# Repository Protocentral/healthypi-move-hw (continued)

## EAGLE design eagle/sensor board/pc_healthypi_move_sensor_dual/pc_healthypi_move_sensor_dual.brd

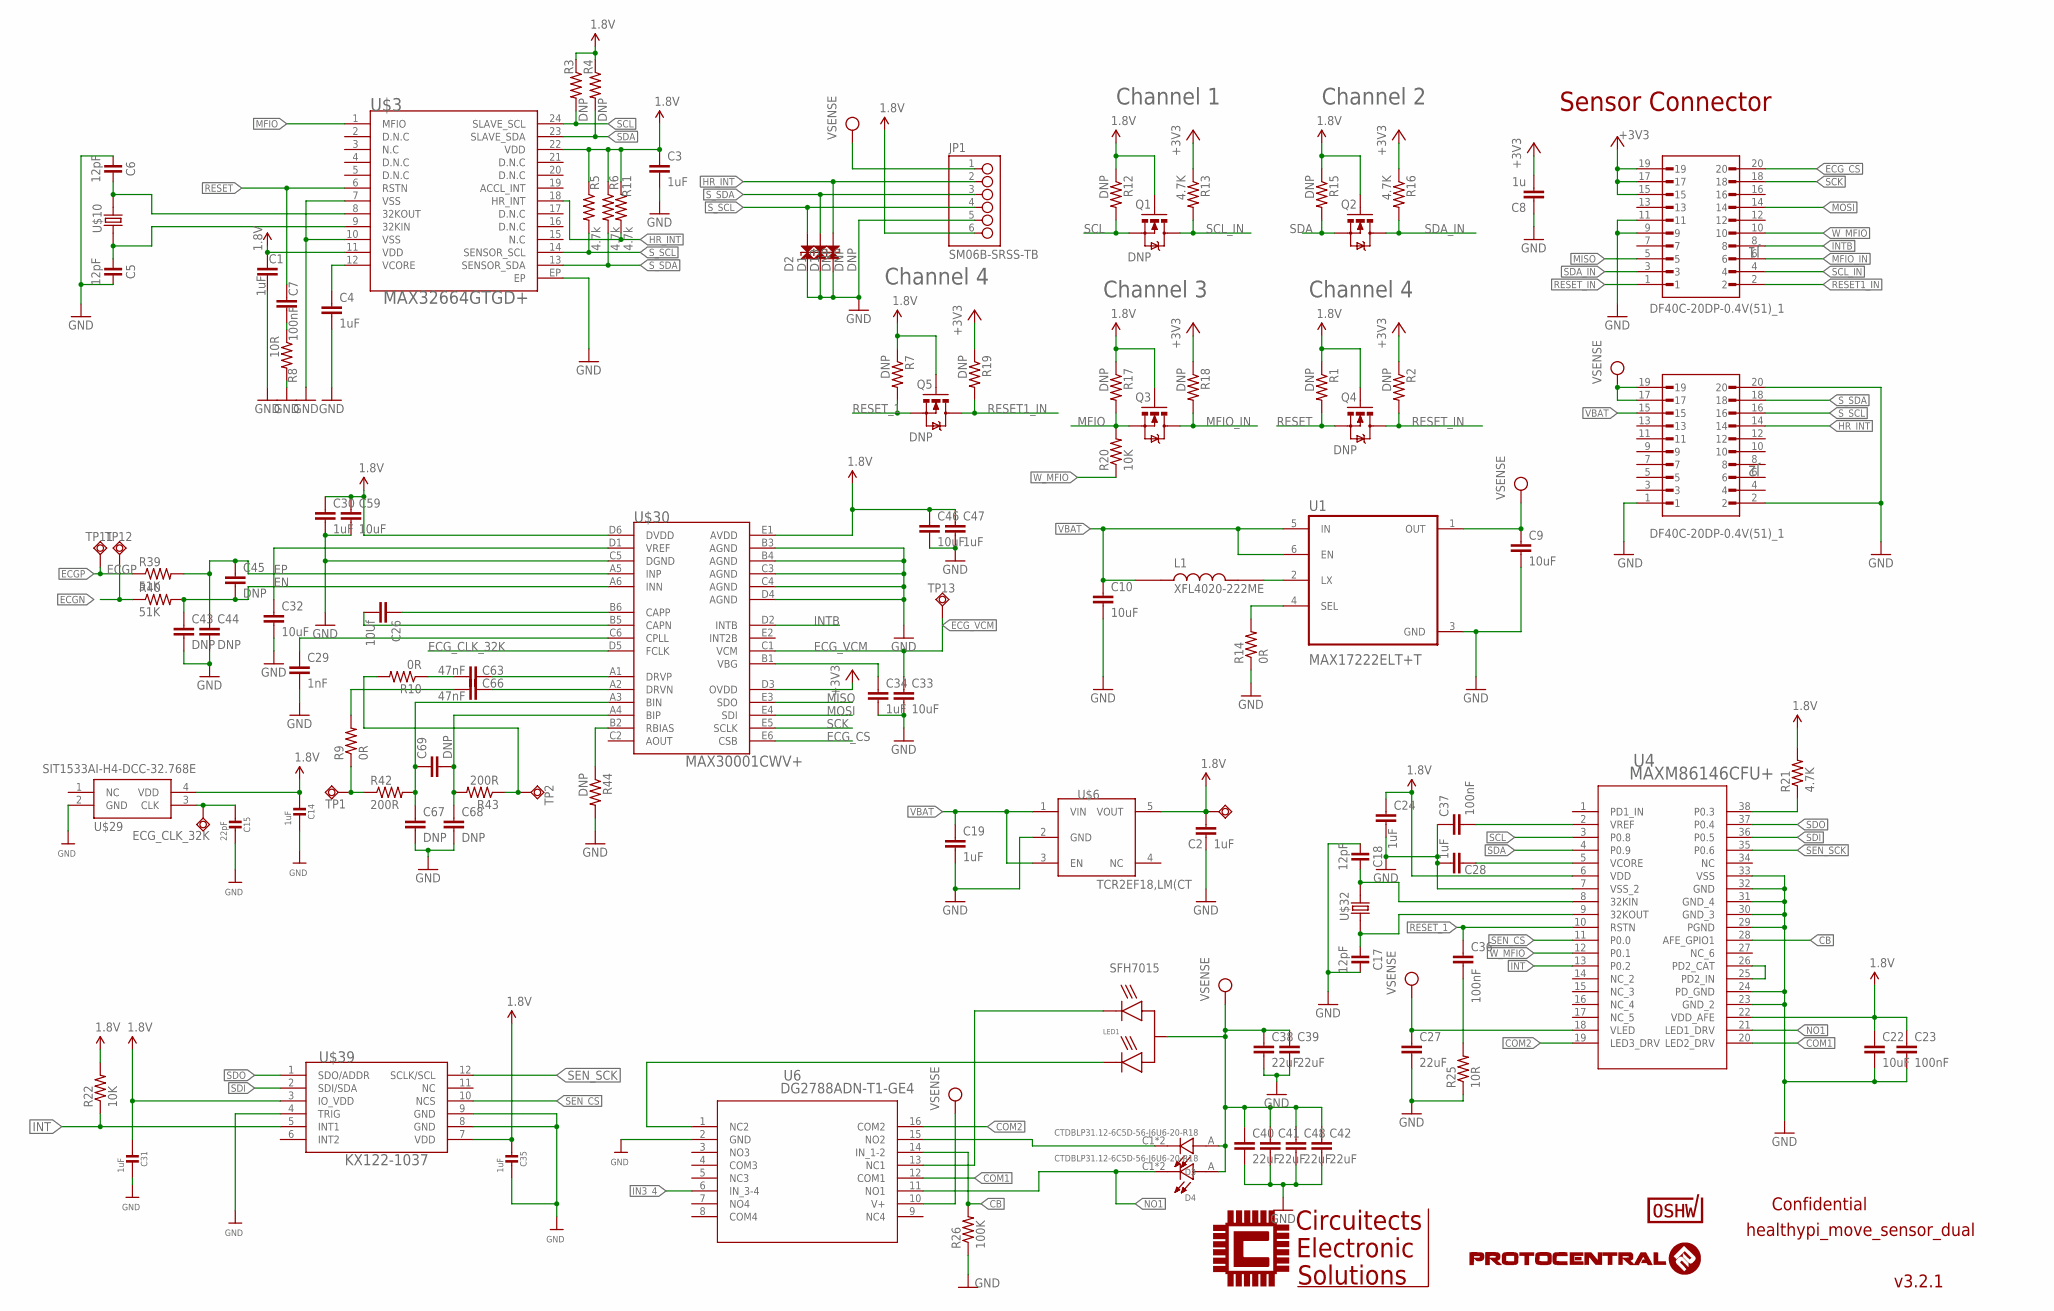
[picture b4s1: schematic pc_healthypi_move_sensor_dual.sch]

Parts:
C1, C2, C3, C4, C19, C24, C28, C30, C34, C47: 1uF; C0402
C5, C6, C17, C18: 12pF; C0402
C7, C23, C36, C37: 100nF; C0402
C8: 1u; C0402
C9, C10, C22, C32, C33, C46, C59: 10uF; C0402
C14, C31, C35: 1uF; 0402
C15: 22pF; 0402
C26: 10Uf; C0402
C27, C38, C39, C40, C41, C42, C48: 22uF; C0805
C29: 1nF; C0402
C43, C44, C45, C67, C68, C69: DNP; C0402
C63, C66: 47nF; C0402
D1, D2, D13: DNP; 0402
D3, D4: CTDBLP31.12-6C5D-56-J6U6-20-R18; LED_CTDBLP31.12-6C5D-56-J6U6-20-R18
J1, J2: DF40C-20DP-0.4V(51)_1; HRS_DF40C-20DP-0.4V(51)
JP1: SM06B-SRSS-TB
L1: XFL4020-222ME; IND_XFL4020-222ME
LED1: SFH7015
Q1, Q2, Q3, Q4, Q5: DNP; SOT23-3
R1, R2, R3, R4, R7, R12, R15, R17, R18, R19, R44: DNP; 0402-RES
R5, R6, R11: 4.7k; 0402-RES
R8: 10R; 0402-RES
R9, R10: 0R; 0402-RES
R13, R16: 4.7K; 0402-RES
R14: 0R; R0402
R20, R22: 10K; 0402-RES
R21: 4.7K; R0402
R25: 10R; R0402
R26: 100K; R0402
R39, R40: 51K; 0402-RES
R42, R43: 200R; 0402-RES
SWIO1, SWIO5: TPSQTP11R; TP11R
TP1, TP2, TP11, TP12, TP13: TPSQTP20SQ; TP20SQ
U1: MAX17222ELT+T; SON65P200X200X80-6N
U4: MAXM86146CFU+; 21-100323A_90-100112A_MXM
U6: DG2788ADN-T1-GE4; MINIQFN-16_VIS
U$3: MAX32664GTGD+; TQFN-24L
U$6: TCR2EF18,LM(CT; SOT95P285X140-5N
U$10, U$32: 520-327-12.5-34B(32.768KHZ); ECX-31B
U$29: SIT1533AI-H4-DCC-32.768E; SIT1533
U$30: MAX30001CWV+; 30WLP
U$39: KX122-1037; KIONIX_KXTJ3-1057
U$48: CERT-SMALL; CERT-SMALL-SILK

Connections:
1.8V: C1.1, C2.1, C3.1, C14.1, C22.1, C23.1, C24.1, C30.1, C31.1, C35.1, C46.1, C47.1, C59.1, JP1.6, Q1.1 (G), Q2.1 (G), Q3.1 (G), Q4.1 (G), Q5.1 (G), R1.1, R3.1, R4.1, R5.1, R6.1, R7.1, R11.1, R12.1, R15.1, R17.1, R21.2, R22.2, SWIO5.TP, U4.6 (VDD), U4.22 (VDD_AFE), U$3.11 (VDD), U$3.22 (VDD), U$6.5 (VOUT), U$29.4 (VDD), U$30.D6 (DVDD), U$30.E1 (AVDD), U$39.3 (IO_VDD), U$39.7 (VDD)
+3V3: C8.2, J1.15, J1.17, J1.19, R2.1, R13.1, R16.1, R18.1, R19.1, U$30.D3 (OVDD)
BIAZP: R10.2, R43.1, TP2.TP
BIOZN: R9.1, R42.1, TP1.TP
CB: R26.2, U4.28 (AFE_GPIO1), U6.14 (IN_1-2)
CLK_32K: C5.1, U$3.9 (32KIN), U$10.P$1 (1)
CLK_32K1: C17.1, U4.9 (32KOUT), U$32.P$1 (1)
COM1: U4.20 (LED2_DRV), U6.12 (COM1)
COM2: U4.19 (LED3_DRV), U6.16 (COM2)
ECGN: R40.1, TP12.TP
ECGP: R39.1, TP11.TP
ECG_CLK_32K: C15.1, SWIO1.TP, U$29.3 (CLK), U$30.D5 (FCLK)
ECG_CS: J1.20, U$30.E6 (CSB)
ECG_VCM: C33.1, TP13.TP, U$30.C1 (VCM)
EN: C43.1, C45.2, R40.2, U$30.A6 (INN)
EP: C44.1, C45.1, R39.2, U$30.A5 (INP)
GND: C1.2, C2.2, C3.2, C4.2, C5.2, C6.1, C8.1, C9.2, C10.2, C14.2, C15.2, C17.2, C18.1, C19.2, C22.2, C23.2, C24.2, C27.2, C28.2, C29.2, C30.2, C31.2, C32.2, C33.2, C34.2, C35.2, C37.1, C38.2, C39.2, C40.2, C41.2, C42.2, C43.2, C44.2, C46.2, C47.2, C48.2, C59.2, C67.2, C68.2, D1.1, D2.1, D13.1, J1.9, J1.11, J2.1, J2.2, J2.20, JP1.5, R8.2, R14.1, R25.1, R26.1, R44.2, U1.3 (GND), U4.7 (VSS_2), U4.23 (GND_2), U4.24 (PD_GND), U4.29 (PGND), U4.30 (GND_3), U4.31 (GND_4), U4.32 (GND), U4.33 (VSS), U6.2 (GND), U$3.7 (VSS), U$3.10 (VSS), U$3.EP, U$6.2 (GND), U$29.2 (GND), U$30.B3 (AGND), U$30.B4 (AGND), U$30.C3 (AGND), U$30.C4 (AGND), U$30.C5 (DGND), U$30.D4 (AGND), U$39.4 (TRIG), U$39.8 (GND), U$39.9 (GND)
HR_INT: D13.2, J2.14, JP1.2, R11.2, U$3.18 (HR_INT)
IN3_4: U6.6 (IN_3-4)
INT: R22.1, U4.13 (P0.2), U$39.5 (INT1)
INTB: J1.8, U$30.D2 (INTB)
MFIO: Q3.2 (S), R17.2, R20.2, U$3.1 (MFIO)
MFIO_IN: J1.6, Q3.3 (D), R18.2
MISO: J1.5, U$30.E3 (SDO)
MOSI: J1.14, U$30.E4 (SDI)
unnamed: C4.1, U$3.12 (VCORE)
unnamed: C7.2, R8.1
unnamed: R14.2, U1.4 (SEL)
unnamed: L1.2, U1.2 (LX)
unnamed: C18.2, U4.8 (32KIN), U$32.P$2 (2)
unnamed: U4.25 (PD2_IN), U4.26 (PD2_CAT)
unnamed: C28.1, U4.5 (VCORE)
unnamed: R21.1, U4.38 (P0.3)
unnamed: C37.2, U4.2 (VREF)
unnamed: C36.2, R25.2
unnamed: C66.1, R9.2
unnamed: C63.1, R10.1
unnamed: LED1.4 (IRC), U6.13 (NC1)
unnamed: LED1.2 (RC), U6.1 (NC2)
unnamed: C6.2, U$3.8 (32KOUT), U$10.P$2 (2)
unnamed: D3.C1 (C), D3.C2 (C), U6.15 (NO2)
unnamed: C29.1, U$30.C6 (CPLL)
unnamed: C26.2, U$30.B5 (CAPN)
unnamed: C32.1, U$30.D1 (VREF)
unnamed: C34.1, U$30.B1 (VBG)
unnamed: C26.1, U$30.B6 (CAPP)
unnamed: C63.2, U$30.A1 (DRVP)
unnamed: C66.2, U$30.A2 (DRVN)
unnamed: C67.1, C69.1, R42.2, U$30.A3 (BIN)
unnamed: C68.1, C69.2, R43.2, U$30.A4 (BIP)
unnamed: R44.1, U$30.B2 (RBIAS)
NO1: D4.C1 (C), D4.C2 (C), U4.21 (LED1_DRV), U6.11 (NO1)
RESET: C7.1, Q4.2 (S), R1.2, U$3.6 (RSTN)
RESET1_IN: J1.2, Q5.3 (D), R19.2
RESET_1: C36.1, Q5.2 (S), R7.2, U4.10 (RSTN)
RESET_IN: J1.1, Q4.3 (D), R2.2
SCK: J1.18, U$30.E5 (SCLK)
SCL: Q1.2 (S), R3.2, R12.2, U4.3 (P0.8), U$3.24 (SLAVE_SCL)
SCL_IN: J1.4, Q1.3 (D), R13.2
SDA: Q2.2 (S), R4.2, R15.2, U4.4 (P0.9), U$3.23 (SLAVE_SDA)
SDA_IN: J1.3, Q2.3 (D), R16.2
SDI: U4.36 (P0.5), U$39.2 (SDI/SDA)
SDO: U4.37 (P0.4), U$39.1 (SDO/ADDR)
SEN_CS: U4.11 (P0.0), U$39.10 (NCS)
SEN_SCK: U4.35 (P0.6), U$39.12 (SCLK/SCL)
S_SCL: D2.2, J2.16, JP1.4, R5.2, U$3.14 (SENSOR_SCL)
S_SDA: D1.2, J2.18, JP1.3, R6.2, U$3.13 (SENSOR_SDA)
VBAT: C10.1, C19.1, J2.15, L1.1, U1.5 (IN), U1.6 (EN), U$6.1 (VIN), U$6.3 (EN)
VPP: C9.1, C27.1, C38.1, C39.1, C40.1, C41.1, C42.1, C48.1, D3.A, D4.A, J2.17, J2.19, JP1.1, LED1.3 (A), U1.1 (OUT), U4.18 (VLED), U6.10 (V+)
W_MFIO: J1.10, R20.1, U4.12 (P0.1)

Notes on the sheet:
v3.2.1
healthypi_move_sensor_dual
Confidential
Channel 1
Channel 2
Channel 3
Channel 4
Sensor Connector
SFH7015

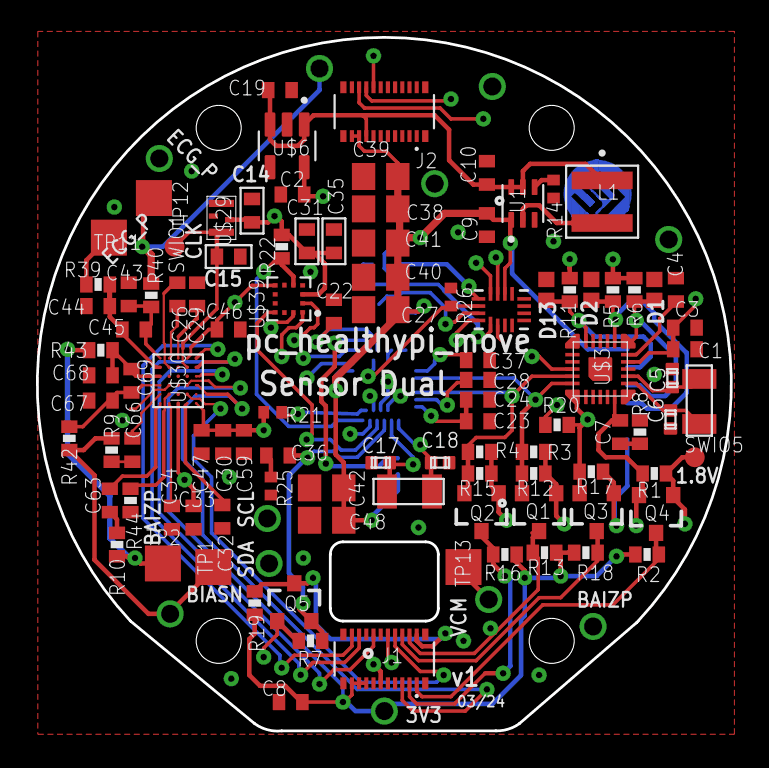
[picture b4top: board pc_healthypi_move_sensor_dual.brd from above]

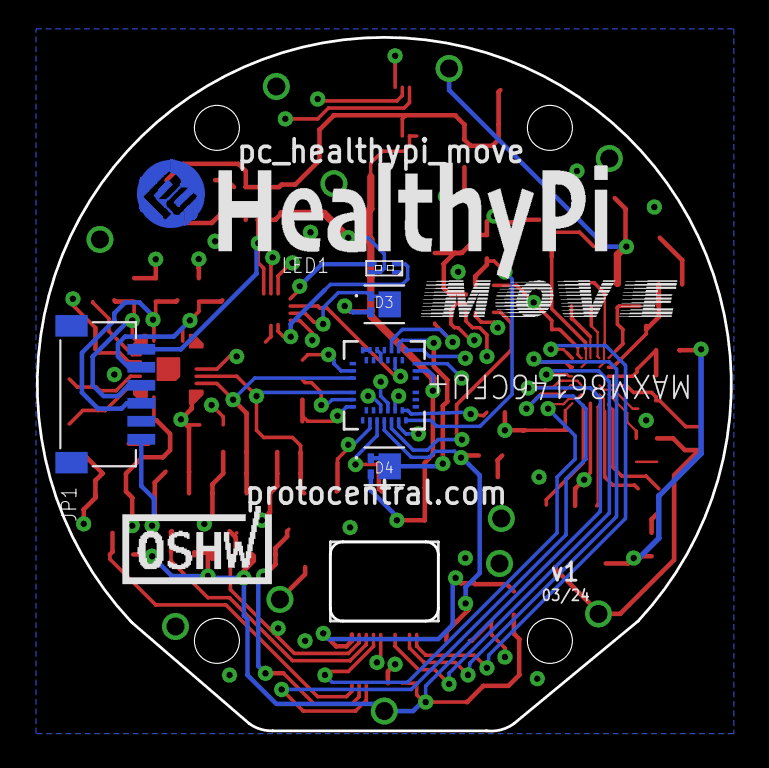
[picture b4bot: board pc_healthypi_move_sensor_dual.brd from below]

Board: 4 copper layers, 38.5 x 38.5 mm, 112 parts (9 on the bottom side), 69 nets.

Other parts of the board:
U$23: HEALTHYPI_MOVE_LOGO_1
U$24: HEALTHYPI_MOVE_LOGO
U$52: PCROUNDLOGO_GOLD
